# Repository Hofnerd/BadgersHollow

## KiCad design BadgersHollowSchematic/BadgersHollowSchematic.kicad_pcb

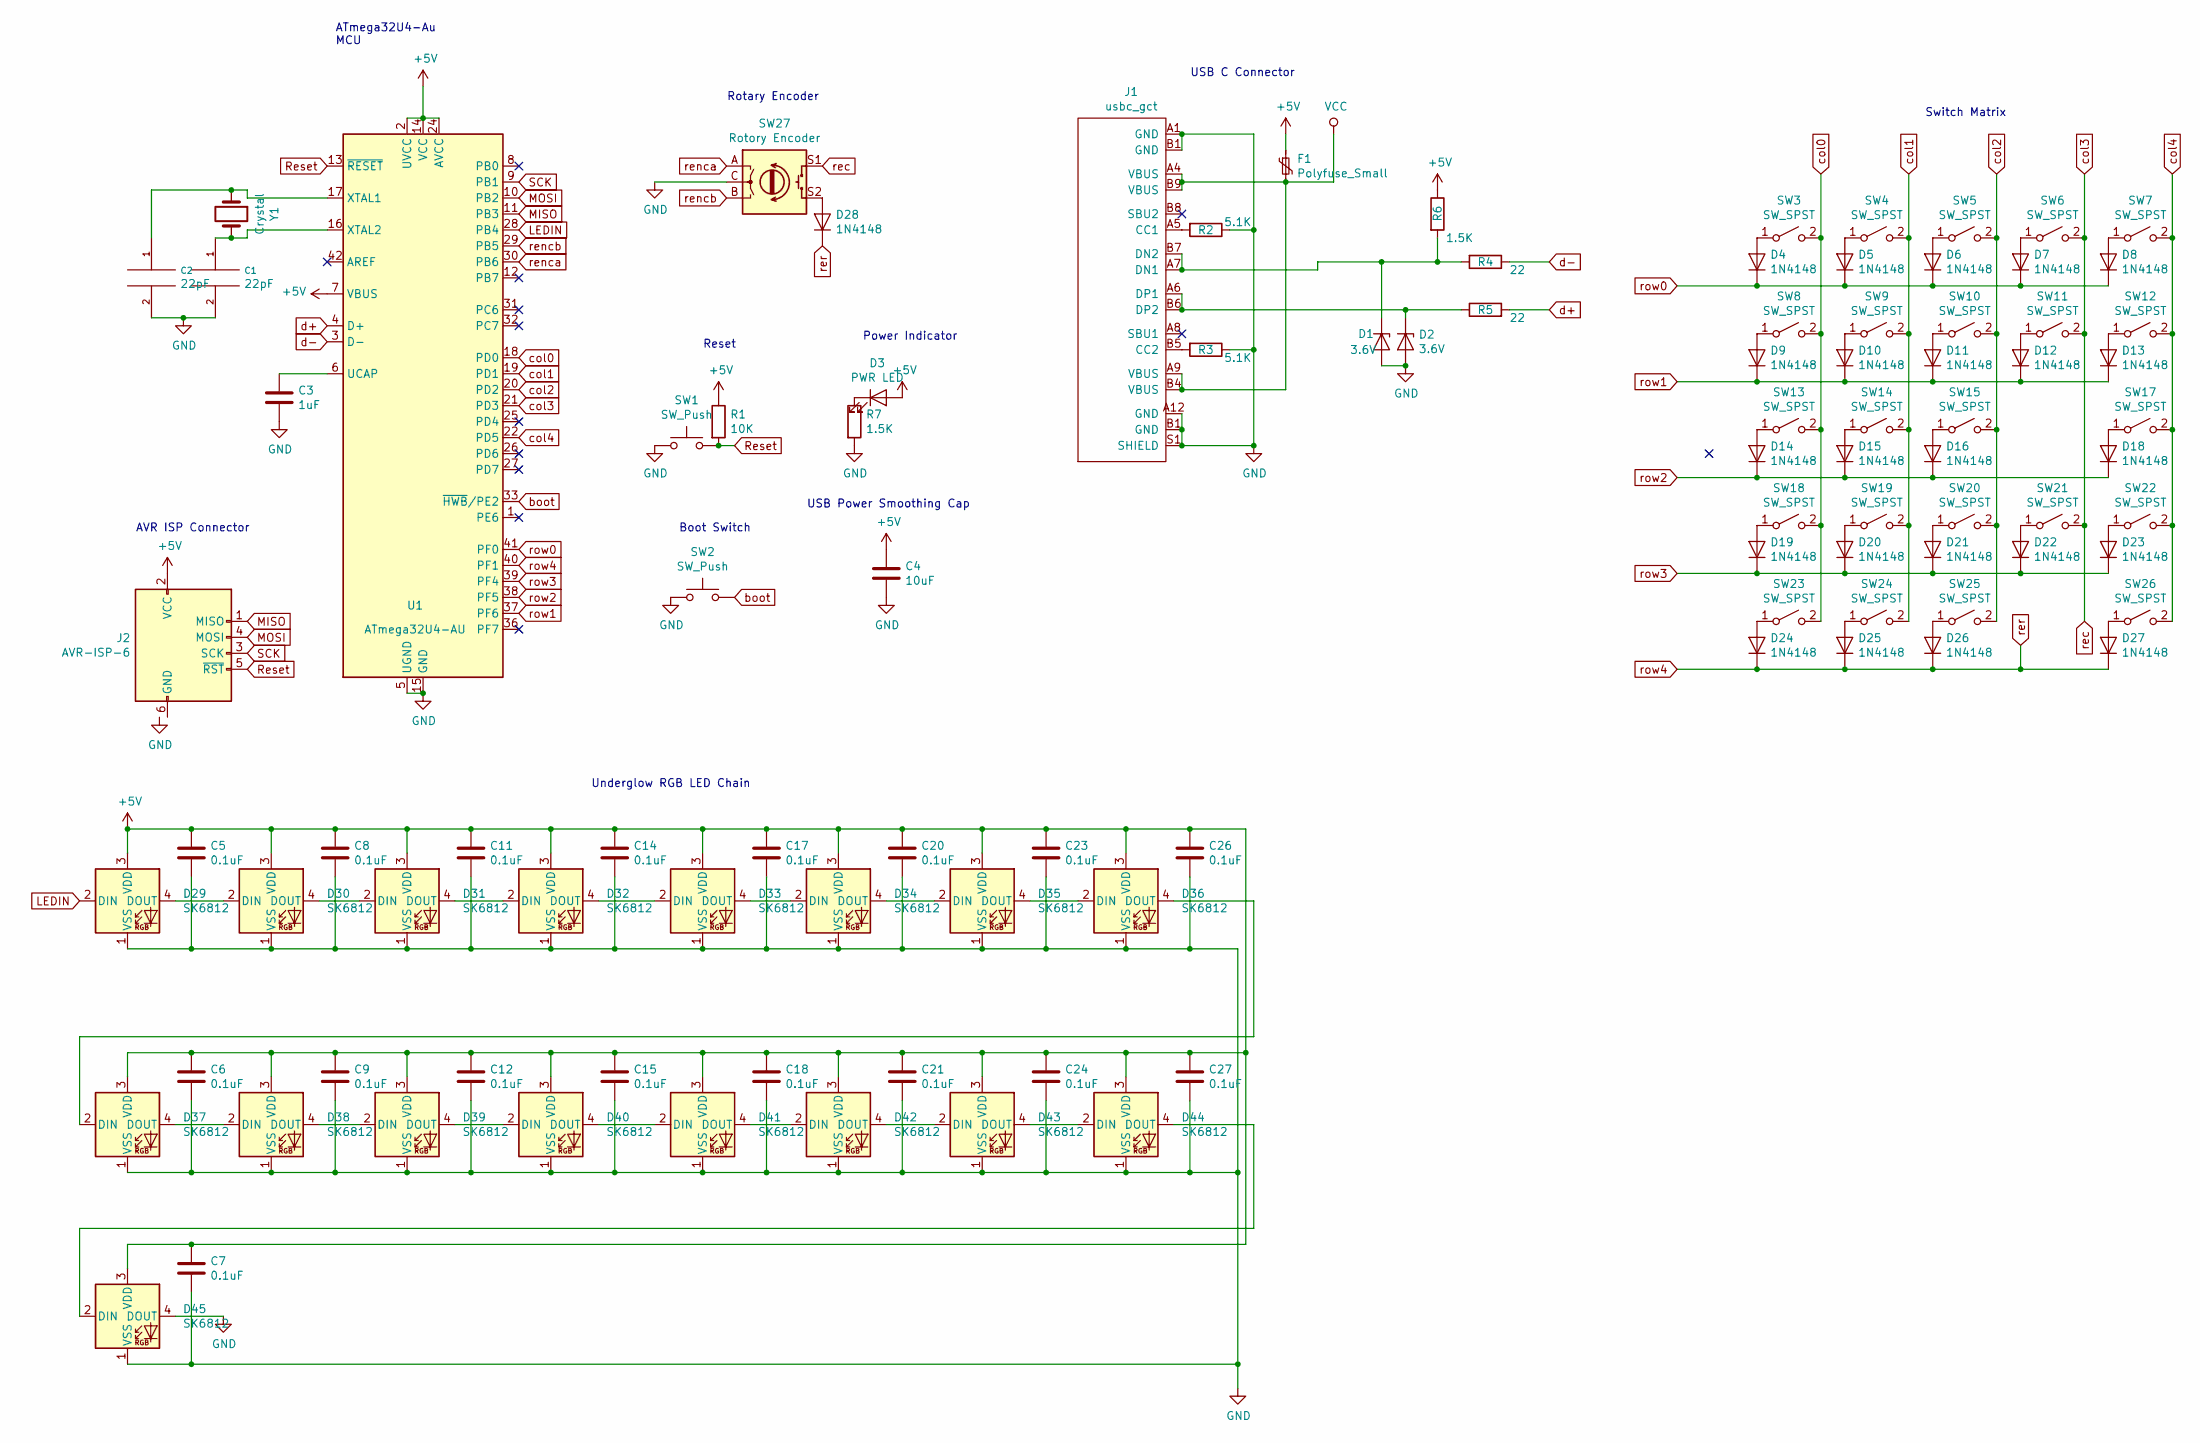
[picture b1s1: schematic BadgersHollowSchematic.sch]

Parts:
C1, C2: 22pF; C_1206_3216Metric_Pad1.42x1.75mm_HandSolder
C3: 1uF; R_1206_3216Metric_Pad1.42x1.75mm_HandSolder
C4: 10uF; C_0603_1608Metric_Pad1.05x0.95mm_HandSolder
C5, C6, C7, C8, C9, C11, C12, C14, C15, C17, C18, C20, C21, C23, C24, C26, C27: 0.1uF; C_0805_2012Metric_Pad1.15x1.40mm_HandSolder
D1, D2: 3.6V; D_DO-41_SOD81_P3.81mm_Vertical_AnodeUp
D3: PWR LED; LED_1206_3216Metric_Pad1.42x1.75mm_HandSolder
D4, D5, D6, D7, D8, D9, D10, D11, D12, D13, D14, D15, D16, D18, D19, D20, D21, D22, D23, D24, D25, D26, D27, D28: 1N4148; D_SOD-323_HandSoldering
D29, D30, D31, D32, D33, D34, D35, D36, D37, D38, D39, D40, D41, D42, D43, D44, D45: SK6812; LED_SK6812_PLCC4_5.0x5.0mm_P3.2mm
F1: Polyfuse_Small; Fuse_1206_3216Metric
J1: usbc_gct; USB_C_Receptacle_GCT_USB4085
J2: AVR-ISP-6; PinHeader_2x03_P2.00mm_Vertical
R1: 10K; R_1206_3216Metric_Pad1.42x1.75mm_HandSolder
R2, R3: 5.1K; R_1206_3216Metric_Pad1.42x1.75mm_HandSolder
R4, R5: 22; R_0805_2012Metric_Pad1.15x1.40mm_HandSolder
R6, R7: 1.5K; R_0805_2012Metric_Pad1.15x1.40mm_HandSolder
SW1, SW2: SW_Push; SW_PUSH_6mm
SW3, SW4, SW5, SW6, SW7, SW8, SW9, SW10, SW12, SW13, SW14, SW15, SW17, SW18, SW19, SW20, SW22, SW23, SW24, SW25, SW26: SW_SPST; SW_Cherry_MX_1.00u_PCB
SW11, SW21: SW_SPST; SW_Cherry_MX_2.00u_Vertical_PCB
SW27: Rotory Encoder; RotaryEncoder_Alps_EC11E-Switch_Vertical_H20mm_CircularMoun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
U1: ATmega32U4-AU; TQFP-44_10x10mm_P0.8mm
Y1: Crystal; Crystal_HC49-U_Vertical

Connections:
+5V: C4.1, C5.1, C6.1, C7.1, C8.1, C9.1, C11.1, C12.1, C14.1, C15.1, C17.1, C18.1, C20.1, C21.1, C23.1, C24.1, C26.1, C27.1, D3.2 (A), D29.3 (VDD), D30.3 (VDD), D31.3 (VDD), D32.3 (VDD), D33.3 (VDD), D34.3 (VDD), D35.3 (VDD), D36.3 (VDD), D37.3 (VDD), D38.3 (VDD), D39.3 (VDD), D40.3 (VDD), D41.3 (VDD), D42.3 (VDD), D43.3 (VDD), D44.3 (VDD), D45.3 (VDD), F1.1, J2.2 (VCC), R1.1, R6.1, U1.2 (UVCC), U1.7 (VBUS), U1.14 (VCC), U1.24 (AVCC), U1.34 (VCC), U1.44 (AVCC)
GND: C1.2, C2.2, C3.2, C4.2, C5.2, C6.2, C7.2, C8.2, C9.2, C11.2, C12.2, C14.2, C15.2, C17.2, C18.2, C20.2, C21.2, C23.2, C24.2, C26.2, C27.2, D1.2 (A), D2.2 (A), D29.1 (VSS), D30.1 (VSS), D31.1 (VSS), D32.1 (VSS), D33.1 (VSS), D34.1 (VSS), D35.1 (VSS), D36.1 (VSS), D37.1 (VSS), D38.1 (VSS), D39.1 (VSS), D40.1 (VSS), D41.1 (VSS), D42.1 (VSS), D43.1 (VSS), D44.1 (VSS), D45.1 (VSS), D45.4 (DOUT), J1.A1 (GND), J1.A12 (GND), J1.B1 (GND), J1.S1 (SHIELD), R2.1, R3.1, R7.2, SW1.1, SW2.1, SW27.C, U1.5 (UGND), U1.15 (GND), U1.23 (GND), U1.35 (GND), U1.43 (GND)
LEDIN: D29.2 (DIN), U1.28 (PB4)
MISO: J2.1 (MISO), U1.11 (PB3)
MOSI: J2.4 (MOSI), U1.10 (PB2)
unnamed: C1.1, U1.16 (XTAL2), Y1.2
unnamed: C2.1, U1.17 (XTAL1), Y1.1
unnamed: C3.1, U1.6 (UCAP)
unnamed: D1.1 (K), J1.A7 (DN1), J1.B7 (DN2), R4.2, R6.2
unnamed: D2.1 (K), J1.A6 (DP1), J1.B6 (DP2), R5.1
unnamed: D3.1 (K), R7.1
unnamed: D4.2 (A), SW3.1 (A)
unnamed: D5.2 (A), SW4.1 (A)
unnamed: D6.2 (A), SW5.1 (A)
unnamed: D7.2 (A), SW6.1 (A)
unnamed: D8.2 (A), SW7.1 (A)
unnamed: D9.2 (A), SW8.1 (A)
unnamed: D10.2 (A), SW9.1 (A)
unnamed: D11.2 (A), SW10.1 (A)
unnamed: D12.2 (A), SW11.1 (A)
unnamed: D13.2 (A), SW12.1 (A)
unnamed: D14.2 (A), SW13.1 (A)
unnamed: D15.2 (A), SW14.1 (A)
unnamed: D16.2 (A), SW15.1 (A)
unnamed: D18.2 (A), SW17.1 (A)
unnamed: D19.2 (A), SW18.1 (A)
unnamed: D20.2 (A), SW19.1 (A)
unnamed: D21.2 (A), SW20.1 (A)
unnamed: D22.2 (A), SW21.1 (A)
unnamed: D23.2 (A), SW22.1 (A)
unnamed: D24.2 (A), SW23.1 (A)
unnamed: D25.2 (A), SW24.1 (A)
unnamed: D26.2 (A), SW25.1 (A)
unnamed: D27.2 (A), SW26.1 (A)
unnamed: D28.2 (A), SW27.S2
unnamed: D29.4 (DOUT), D30.2 (DIN)
unnamed: D30.4 (DOUT), D31.2 (DIN)
unnamed: D31.4 (DOUT), D32.2 (DIN)
unnamed: D32.4 (DOUT), D33.2 (DIN)
unnamed: D33.4 (DOUT), D34.2 (DIN)
unnamed: D34.4 (DOUT), D35.2 (DIN)
unnamed: D35.4 (DOUT), D36.2 (DIN)
unnamed: D36.4 (DOUT), D37.2 (DIN)
unnamed: D37.4 (DOUT), D38.2 (DIN)
unnamed: D38.4 (DOUT), D39.2 (DIN)
unnamed: D39.4 (DOUT), D40.2 (DIN)
unnamed: D40.4 (DOUT), D41.2 (DIN)
unnamed: D41.4 (DOUT), D42.2 (DIN)
unnamed: D42.4 (DOUT), D43.2 (DIN)
unnamed: D43.4 (DOUT), D44.2 (DIN)
unnamed: D44.4 (DOUT), D45.2 (DIN)
unnamed: J1.A5 (CC1), R2.2
unnamed: J1.B5 (CC2), R3.2
Reset: J2.5 (~RST), R1.2, SW1.2, U1.13 (~RESET)
SCK: J2.3 (SCK), U1.9 (PB1)
VCC: F1.2, J1.A4 (VBUS), J1.A9 (VBUS), J1.B4 (VBUS), J1.B9 (VBUS)
boot: SW2.2, U1.33 (~HWB~/PE2)
col0: SW3.2 (B), SW8.2 (B), SW13.2 (B), SW18.2 (B), SW23.2 (B), U1.18 (PD0)
col1: SW4.2 (B), SW9.2 (B), SW14.2 (B), SW19.2 (B), SW24.2 (B), U1.19 (PD1)
col2: SW5.2 (B), SW10.2 (B), SW15.2 (B), SW20.2 (B), SW25.2 (B), U1.20 (PD2)
col3: SW6.2 (B), SW11.2 (B), SW21.2 (B), SW27.S1, U1.21 (PD3)
col4: SW7.2 (B), SW12.2 (B), SW17.2 (B), SW22.2 (B), SW26.2 (B), U1.22 (PD5)
d+: R5.2, U1.4 (D+)
d-: R4.1, U1.3 (D-)
renca: SW27.A, U1.30 (PB6)
rencb: SW27.B, U1.29 (PB5)
rer: D24.1 (K), D25.1 (K), D26.1 (K), D27.1 (K), D28.1 (K), U1.40 (PF1)
row0: D4.1 (K), D5.1 (K), D6.1 (K), D7.1 (K), D8.1 (K), U1.41 (PF0)
row1: D9.1 (K), D10.1 (K), D11.1 (K), D12.1 (K), D13.1 (K), U1.37 (PF6)
row2: D14.1 (K), D15.1 (K), D16.1 (K), D18.1 (K), U1.38 (PF5)
row3: D19.1 (K), D20.1 (K), D21.1 (K), D22.1 (K), D23.1 (K), U1.39 (PF4)

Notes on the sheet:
USB C Connector
Rotary Encoder
ATmega32U4-Au MCU
Reset
Boot Switch
Power Indicator
USB Power Smoothing Cap
AVR ISP Connector
Underglow RGB LED Chain
Switch Matrix

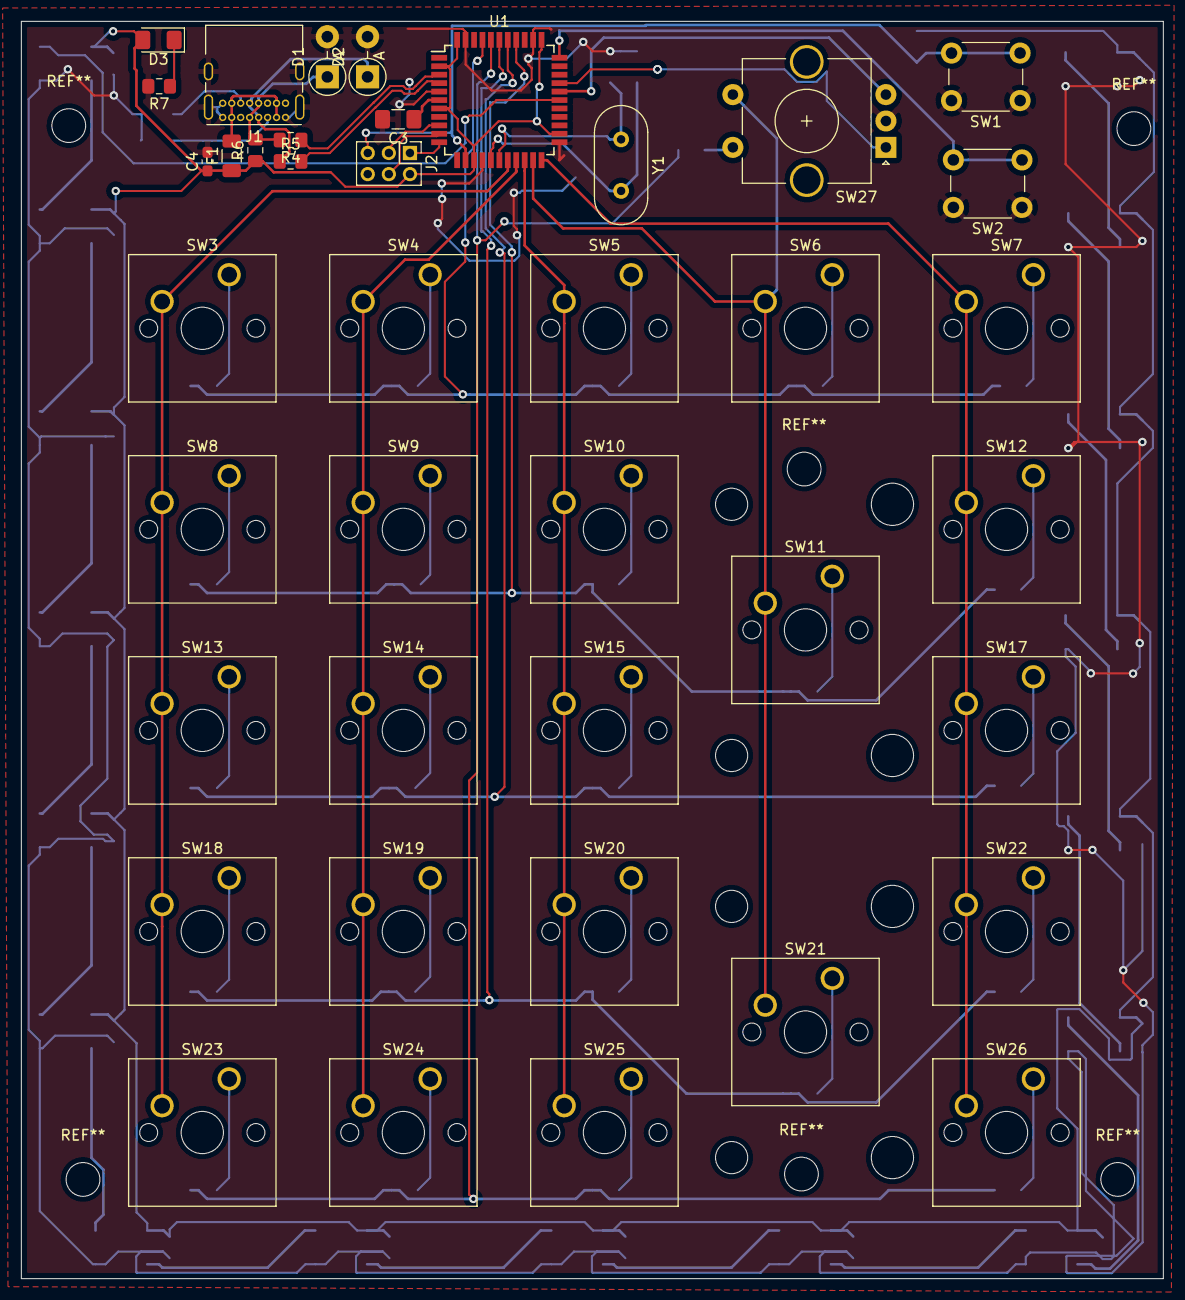
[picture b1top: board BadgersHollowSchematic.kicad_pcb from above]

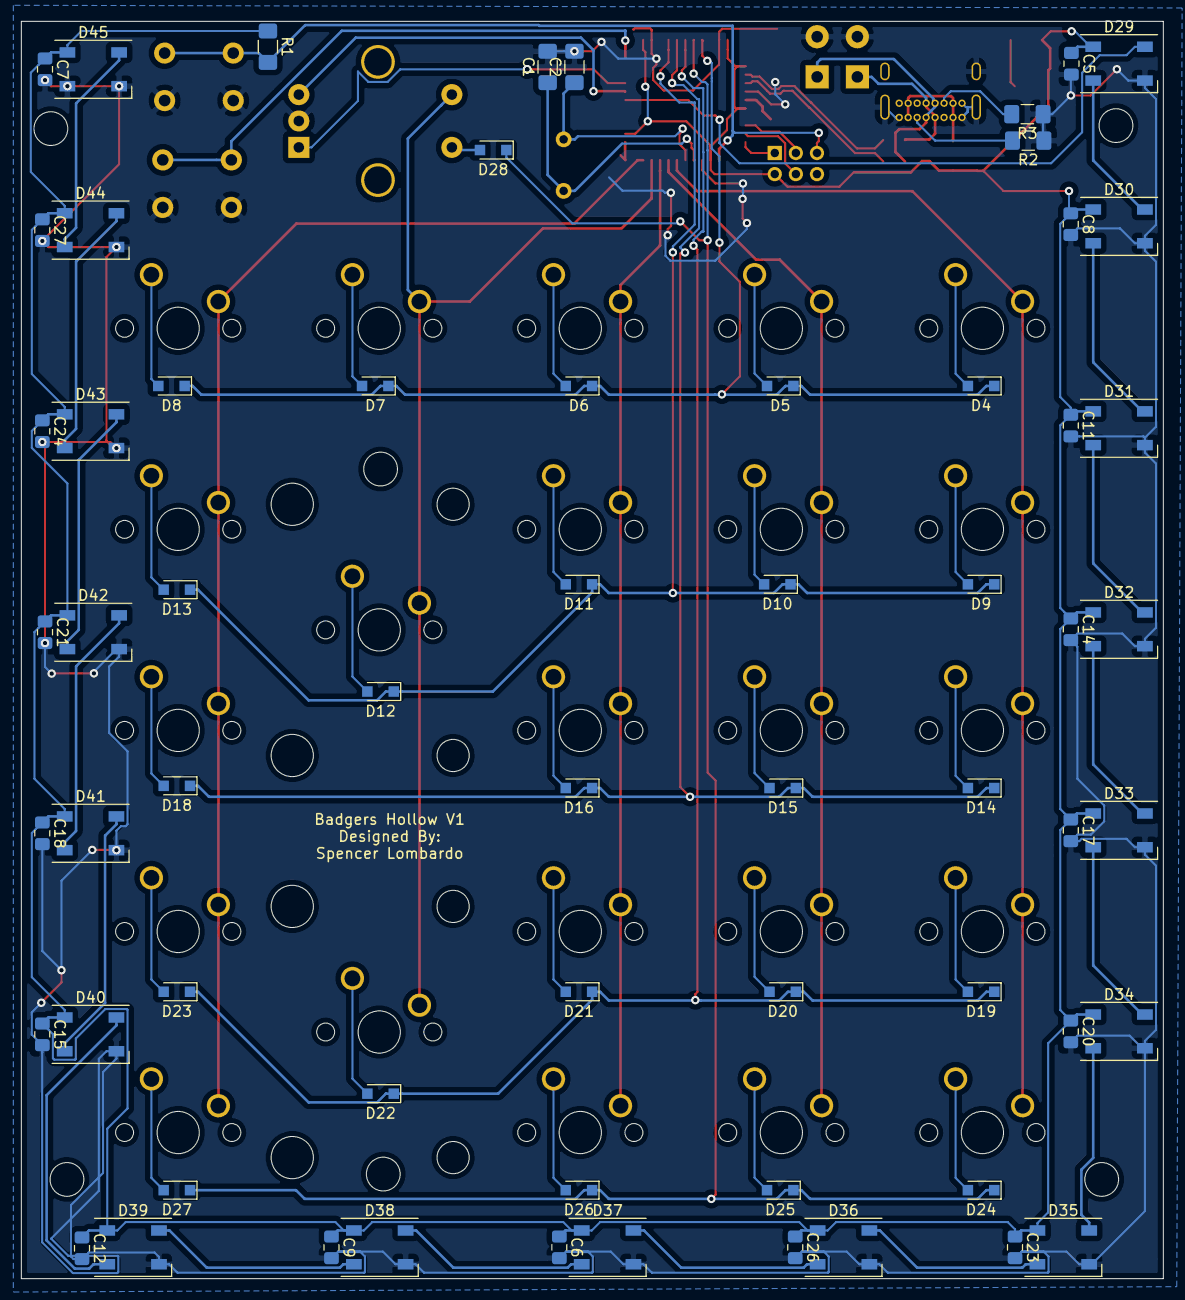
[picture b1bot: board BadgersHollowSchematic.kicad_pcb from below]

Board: 2 copper layers, 108.2 x 119.1 mm, 103 parts (63 on the bottom side), 71 nets.

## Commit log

2020-09-11 Schematic start, testing kicad fucntionality on new dev platform
2020-09-15 Schematic start. mcu and oscillator added
2020-09-15 Removed unneeded directories
2020-09-17 Schematic down. Need to review, and map columns/rows to correct pins
2020-09-17 Finished Schematic, needs to be reviewed then moved to layout
2020-09-17 Working on layout
2020-09-17 Layout done. Now working on routing
2020-09-20 First rev of the board, with gbr files
2020-09-27 BOE update
2020-09-27 Finialized Bill of Materials with sample components/links
2020-09-27 Final commit before the first round of pcb purchases
2020-10-02 Updated Push
2020-10-02 Updated usbb differential track lengths
2020-10-02 Final V1 before first test run order
